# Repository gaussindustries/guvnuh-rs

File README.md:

# Guv'nuh — Micro-Grid Governor Control Platform

A Rust, bare-metal-to-browser control system for a laboratory micro-grid generator set. A hard-real-time STM32H753 governs the machine; an ESP32 bridges it to a Dioxus server and a desktop operator console. Built as the engineering centerpiece for [Gauss Industries](https://gaussindustri.es).

---

## What it does

Guv'nuh closes the loop on a self-excited induction generator (SEIG) driven by a variable-speed prime mover: it holds speed and frequency against changing electrical load, sheds load safely on fault, and streams a full electrical picture — per-phase voltage and current, real power, power factor, DC-bus state — to an operator in real time.

The architecture follows one principle: **the STM32 runs the machine; everything else observes and commands.** Safety-critical decisions (overspeed, load rejection, over-voltage/current) are computed and acted on locally, on-device, with no dependence on the network being up. The ESP32 relays; the server stores; the terminal analyzes. Comms can drop without the machine ever losing control.

---

## System architecture

```
  ┌─────────────┐   UART/COBS    ┌──────────┐    TCP/COBS    ┌──────────────┐   HTTP    ┌───────────────┐
  │  STM32H753  │◄──────────────►│  ESP32   │◄──────────────►│ Dioxus Server│◄─────────►│ Desktop Term. │
  │  (RTIC 2)   │  telemetry ▲   │ (Embassy)│  telemetry ▲   │   + SurrealDB│           │  (Dioxus)     │
  │  the machine│  commands  ▼   │  bridge  │  commands  ▼   │   store/API  │           │  operator UI  │
  └─────────────┘                └──────────┘                └──────────────┘           └───────────────┘
        │
        ├─ dual ADS131M04 (3-phase V/I + DC bus) — coherent sampling
        ├─ TIM1 PWM → prime-mover drive
        ├─ TIM2 QEI → speed encoder
        └─ ordered load bank (2-step resistive, series-ground)
```

**One wire format, end to end.** Every hop serializes the same `shared` crate types with `postcard` + COBS framing — no translation layers, no schema drift between tiers (the whole set rebuilds together when the wire types change).

---

## The STM32H753 firmware — the real-time core

Written against **RTIC 2**, priority-scheduled so the machine stays in tolerance regardless of what else is happening:

| Priority | Task | Rate | Job |
|---|---|---|---|
| 3 | ADC DRDY ISR | ~4 kSPS | Read both ADCs coherently, accumulate sum-of-squares |
| 3 | UART4 RX ISR | event | Drain FIFO, COBS-decode commands into a queue |
| 2 | Safety supervisor | 500 Hz | Overspeed trip + fast electrical protection + load-rejection detection |
| 1 | Control loop | 100 Hz | Governing, full ADC finalize, telemetry assembly |

**Three-phase electrical measurement.** Two ADS131M04 24-bit delta-sigma ADCs share one SPI bus with tied SYNC lines, so all eight channels sample the *same instant* — essential for real-power math (V×I per phase must be coherent). The STM32 computes only the control-critical scalars locally (RMS V/I, real power, PF, frequency, DC bus); harmonics and deep analysis are left to the terminal. Sample rate is a single tunable constant, sized against measured worst-case execution time.

**Load rejection — the fast local path.** A sudden real-power drop means the generator has been unloaded and will overspeed (the defining hazard for a turbine prime mover). The 500 Hz supervisor watches total real power and reacts in-loop — shedding load and faulting — with no network round-trip. This is why the electrical measurements live on the STM32 and not just in telemetry.

**Ordered load bank.** A two-step resistive bank whose second stage draws its ground return *through* the first, so the switching order is a hard electrical constraint. The firmware models this as a state machine that makes an invalid state unrepresentable: it refuses to engage step 2 without step 1, sheds gracefully (2 then 1) under normal operation, and sheds immediately (open 1, dropping both) on E-stop or fault.

---

## The ESP32 bridge

An **Embassy** async firmware that does one job well: shuttle framed bytes between the STM32's UART and a TCP socket to the server, intercepting the link-layer handshake locally so a reboot on either side re-syncs without disturbing the machine. Deliberately dumb — it holds no control logic, matching the "STM32 runs the machine" principle.

---

## Server & operator console

**Dioxus fullstack server** (axum + SurrealDB): ingests telemetry over TCP, stores trials, and exposes a hardware-control API. Telemetry x-axes are derived from a **server-side frame index**, not the device clock — eliminating boot-offset artifacts by construction.

**Desktop operator terminal** (Dioxus): live governing controls (manual / open-loop / closed-loop / scripted profiles), real-time charts (RPM, three-phase voltage and current on shared axes, power and phase-alignment error), a load-bank panel that mirrors the firmware's ordered state machine in the UI, and a trials browser that replays any recorded run with every electrical channel toggleable.

**Scripted profiles** let an operator define an RPM trajectory with load steps scheduled at specific breakpoints — "at t=5s apply half load, at t=10s go full, at t=15s shed" — executed on-device with the ordered switching still enforced.

---

## Tech stack

- **Firmware:** Rust, `no_std`, RTIC 2 (STM32H753), Embassy (ESP32)
- **Wire format:** `postcard` + COBS over UART and TCP; shared type crate
- **Server:** Rust, Dioxus fullstack, axum, SurrealDB (raw HTTP transport)
- **Terminal:** Rust, Dioxus desktop
- **Sensing:** dual TI ADS131M04, external 8.192 MHz coherent clock
- **Networking:** WireGuard-gated admin plane, nginx reverse proxy

---

## Status

Operational: full command + telemetry pipeline live across all four tiers; load bank commanding end-to-end with ordered-switching and E-stop shedding verified in hardware; governing loop running closed on the bench. Three-phase ADC front-end is wired into the firmware (flag-gated) and pending analog front-end bring-up.

**Roadmap:** phase-lock to a grid reference (the alignment view is built and waiting), EtherCAT fieldbus, a SIL-2 certification path, and a micro steam turbine prime mover.

---

## License

© Gauss Industries. All rights reserved.

*Integrity · Innovation · Invention*

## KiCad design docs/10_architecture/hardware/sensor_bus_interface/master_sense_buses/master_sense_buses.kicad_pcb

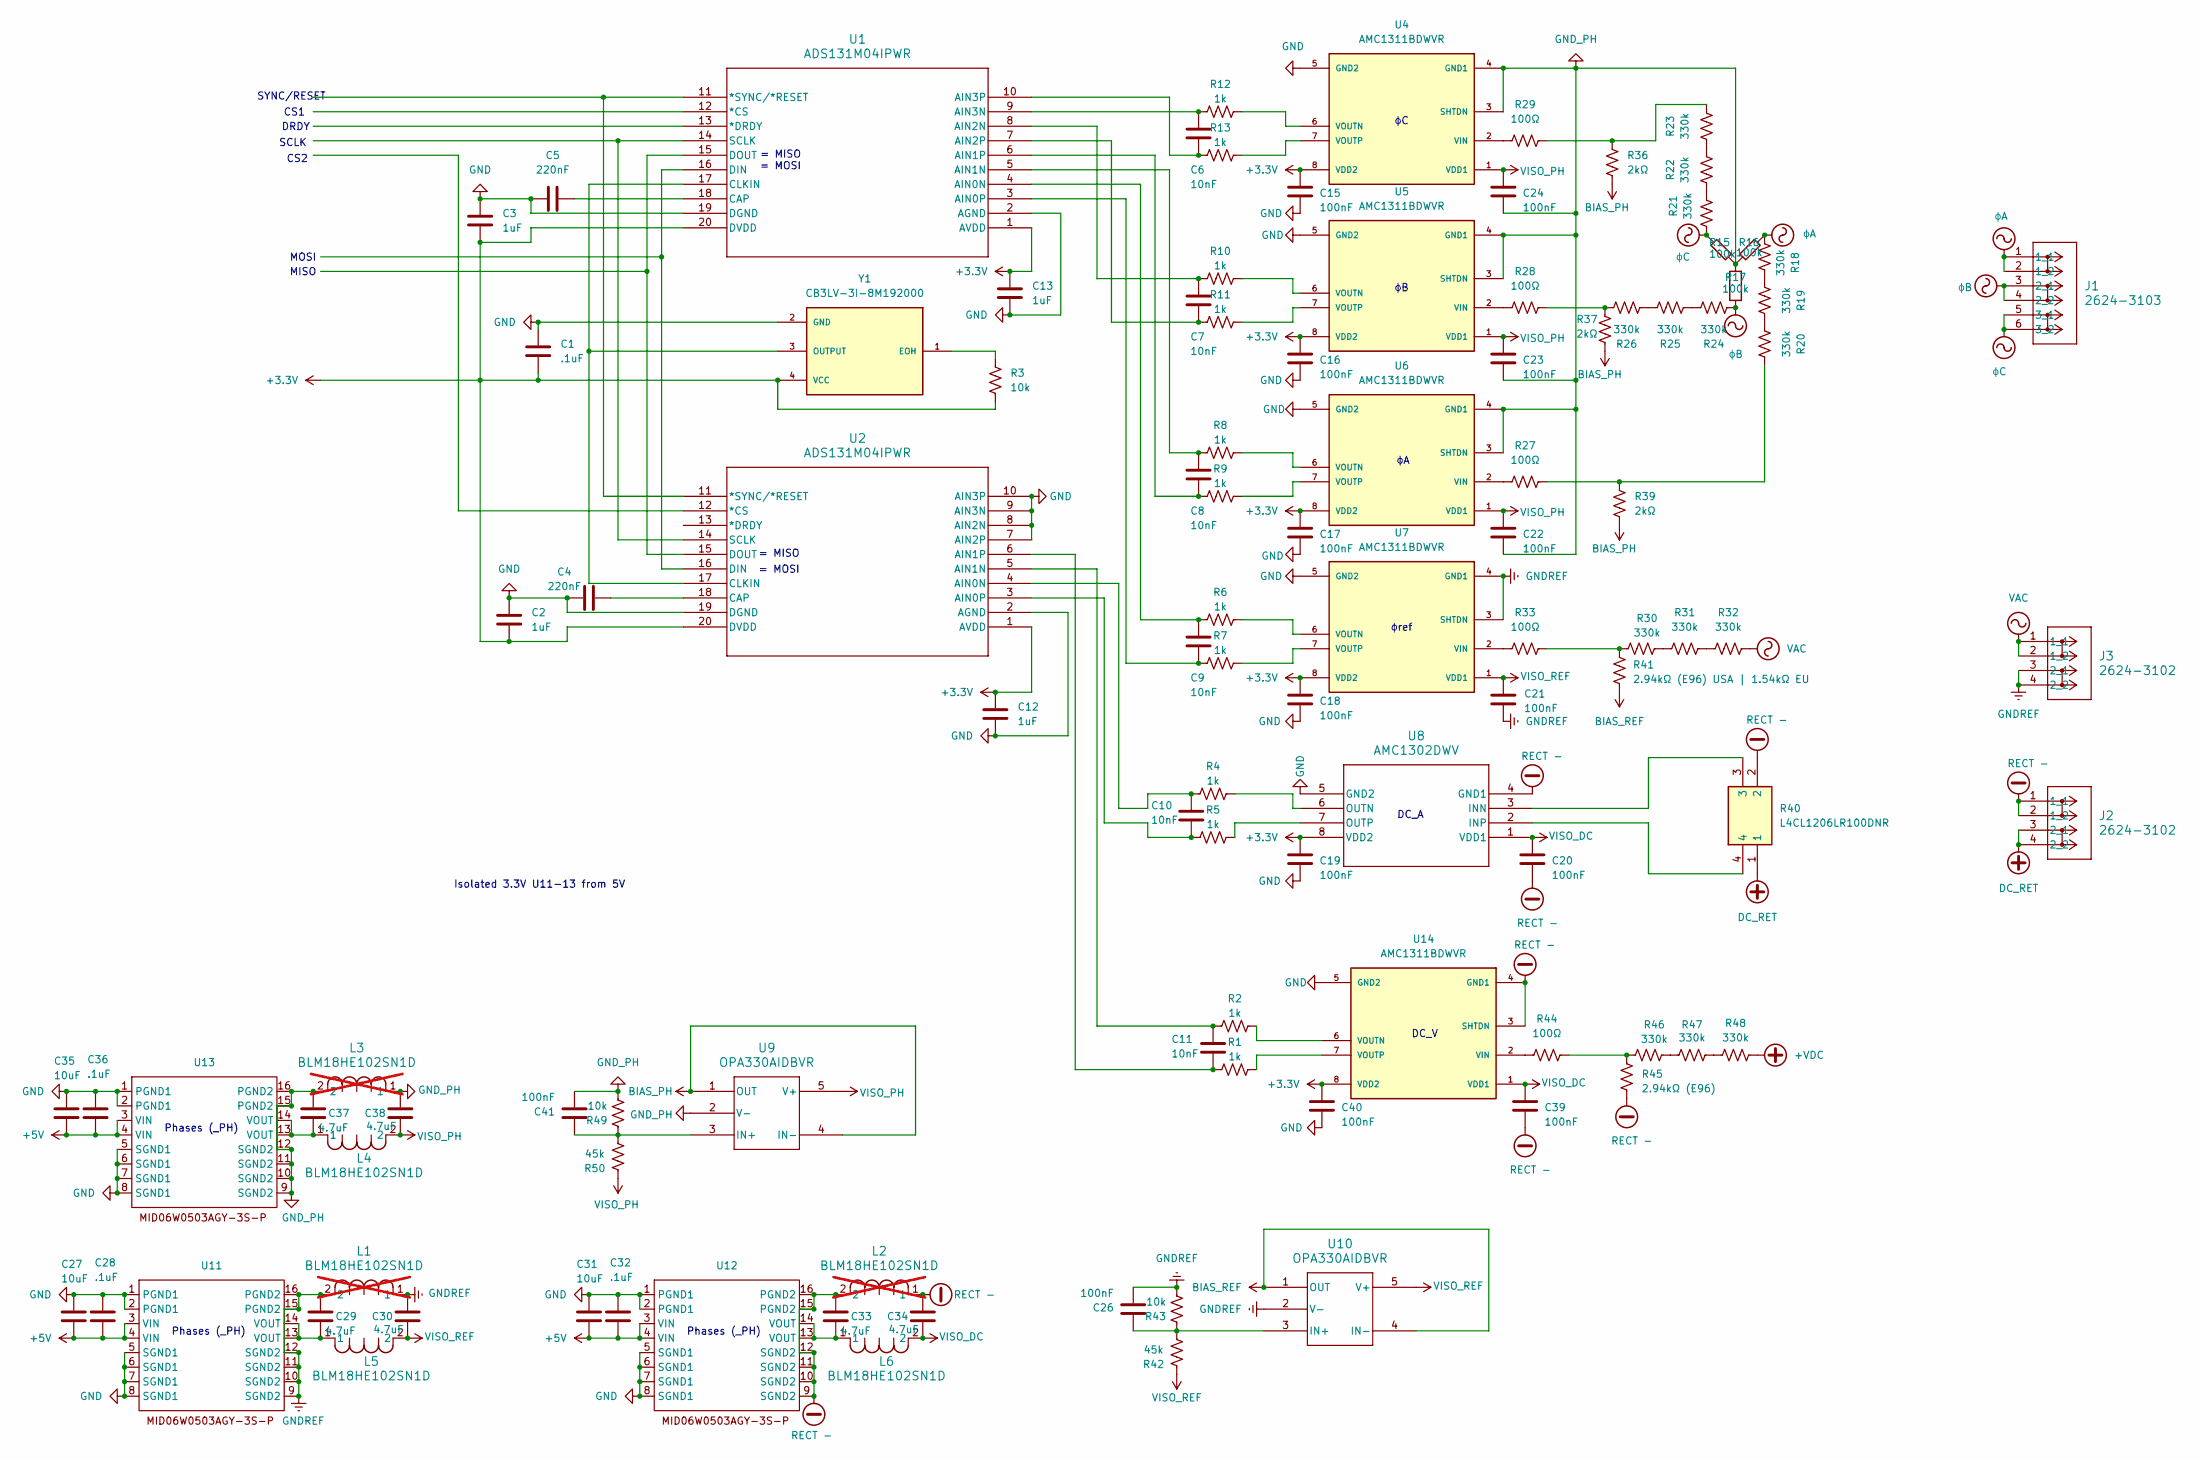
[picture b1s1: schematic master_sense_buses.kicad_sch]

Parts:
C1, C28, C32, C36: .1uF; C_0402_1005Metric
C2, C3, C12, C13: 1uF; C_0603_1608Metric
C4, C5: 220nF; C_0201_0603Metric
C6, C7, C8, C9, C10, C11: 10nF; C_0603_1608Metric
C15, C16, C17, C18, C19, C20, C21, C22, C23, C24, C39, C40: 100nF; C_0402_1005Metric
C26, C41: 100nF; C_0201_0603Metric
C27, C31, C35: 10uF; C_0805_2012Metric
C29, C30, C33, C34, C37, C38: 4.7uF; C_0603_1608Metric
J1: 2624-3103; CONN3_2624-3103_WAG
J2, J3: 2624-3102; CONN2_2624-3102_WAG
L1, L2, L3: BLM18HE102SN1D; IND_BLM18_0603_MUR-L; not fitted
L4, L5, L6: BLM18HE102SN1D; IND_BLM18_0603_MUR-L
R1, R2, R4, R5, R6, R7, R8, R9, R10, R11, R12, R13: 1k; R_0603_1608Metric
R3, R43, R49: 10k; R_0201_0603Metric
R15, R16, R17: 100k; R_Axial_DIN0414_L11.9mm_D4.5mm_P15.24mm_Horizontal
R18, R19, R20, R21, R22, R23, R24, R25, R26, R30, R31, R32, R46, R47, R48: 330k; R_1206_3216Metric
R27, R28, R29, R33, R44: 100Ω; R_0805_2012Metric
R36, R37, R39: 2kΩ; R_1206_3216Metric
R40: L4CL1206LR100DNR; Mouser Part Number 576-L4CL1206LR100DNR
R41: 2.94kΩ (E96) USA | 1.54kΩ EU; R_0402_1005Metric
R42, R50: 45k; R_0603_1608Metric
R45: 2.94kΩ (E96); R_0402_1005Metric
U1, U2: ADS131M04IPWR; PW20_TEX-L
U4, U5, U6, U7, U14: AMC1311BDWVR; SOIC127P1150X280-8N; PARTREV A
U8: AMC1302DWV; SOIC8_DMV_TEX-L
U9, U10: OPA330AIDBVR; DBV5
U11, U12, U13: SOIC-16W_7.5x10.3mm_P1.27mm_MPS_SOICW-16
Y1: CB3LV-3I-8M192000; OSC_CB3LV-3I-8M192000; PARTREV NA

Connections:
+3.3V: C1.2, C2.2, C3.2, C12.1, C13.1, C15.1, C16.1, C17.1, C18.1, C19.1, C40.1, R3.2, U1.1 (AVDD), U1.20 (DVDD), U2.1 (AVDD), U2.20 (DVDD), U4.8 (VDD2), U5.8 (VDD2), U6.8 (VDD2), U7.8 (VDD2), U8.8 (VDD2), U14.8 (VDD2), Y1.4 (VCC)
+5V: C27.2, C28.2, C31.2, C32.2, C35.2, C36.2, U11.3 (VIN), U11.4 (VIN), U12.3 (VIN), U12.4 (VIN), U13.3 (VIN), U13.4 (VIN)
+VDC: R48.1; also elsewhere on the board
BIAS_PH: R36.2, R37.2, R39.2, U9.1 (OUT), U9.4 (IN-)
BIAS_REF: R41.2, U10.1 (OUT), U10.4 (IN-)
DC_RET: J2.3 (2_1), J2.4 (2_2), R40.1
GND: C1.1, C2.1, C3.1, C4.2, C5.1, C12.2, C13.2, C15.2, C16.2, C17.2, C18.2, C19.2, C27.1, C28.1, C31.1, C32.1, C35.1, C36.1, C40.2, U1.2 (AGND), U1.19 (DGND), U2.2 (AGND), U2.7 (AIN2P), U2.8 (AIN2N), U2.9 (AIN3N), U2.10 (AIN3P), U2.19 (DGND), U4.5 (GND2), U5.5 (GND2), U6.5 (GND2), U7.5 (GND2), U8.5 (GND2), U11.1 (PGND1), U11.2 (PGND1), U11.5 (SGND1), U11.6 (SGND1), U11.7 (SGND1), U11.8 (SGND1), U12.1 (PGND1), U12.2 (PGND1), U12.5 (SGND1), U12.6 (SGND1), U12.7 (SGND1), U12.8 (SGND1), U13.1 (PGND1), U13.2 (PGND1), U13.5 (SGND1), U13.6 (SGND1), U13.7 (SGND1), U13.8 (SGND1), U14.5 (GND2), Y1.2 (GND)
GNDREF: C21.2, C26.2, C29.1, C30.1, J3.3 (2_1), J3.4 (2_2), L1.1, L1.2, R43.2, U7.3 (SHTDN), U7.4 (GND1), U10.2 (V-), U11.9 (SGND2), U11.10 (SGND2), U11.11 (SGND2), U11.12 (SGND2), U11.15 (PGND2), U11.16 (PGND2)
GND_PH: C22.2, C23.2, C24.2, C37.1, C38.1, C41.2, L3.1, L3.2, R15.1, R16.2, R17.2, R49.2, U4.3 (SHTDN), U4.4 (GND1), U5.3 (SHTDN), U5.4 (GND1), U6.3 (SHTDN), U6.4 (GND1), U9.2 (V-), U13.9 (SGND2), U13.10 (SGND2), U13.11 (SGND2), U13.12 (SGND2), U13.15 (PGND2), U13.16 (PGND2)
unnamed: C29.2, L5.1, U11.13 (VOUT), U11.14 (VOUT)
unnamed: C33.2, L6.1, U12.13 (VOUT), U12.14 (VOUT)
unnamed: C37.2, L4.1, U13.13 (VOUT), U13.14 (VOUT)
unnamed: R18.1, R19.2
unnamed: R19.1, R20.2
unnamed: R20.1, R27.1, R39.1
unnamed: R21.1, R22.2
unnamed: R22.1, R23.2
unnamed: R23.1, R29.1, R36.1
unnamed: R24.1, R25.2
unnamed: R25.1, R26.2
unnamed: R26.1, R28.1, R37.1
unnamed: R30.1, R31.2
unnamed: R30.2, R33.1, R41.1
unnamed: R31.1, R32.2
unnamed: R44.1, R45.1, R46.2
unnamed: R46.1, R47.2
unnamed: R47.1, R48.2
unnamed: U1.11 (*SYNC/*RESET), U2.11 (*SYNC/*RESET)
unnamed: C9.1, R6.2, U1.4 (AIN0N)
unnamed: C9.2, R7.2, U1.3 (AIN0P)
unnamed: C8.1, R8.2, U1.5 (AIN1N)
unnamed: C8.2, R9.2, U1.6 (AIN1P)
unnamed: C7.1, R10.2, U1.8 (AIN2N)
unnamed: C7.2, R11.2, U1.7 (AIN2P)
unnamed: C6.1, R12.2, U1.9 (AIN3N)
unnamed: C6.2, R13.2, U1.10 (AIN3P)
unnamed: C5.2, U1.18 (CAP)
unnamed: U1.17 (CLKIN), U2.17 (CLKIN), Y1.3 (OUTPUT)
unnamed: U1.16 (DIN), U2.16 (DIN)
unnamed: U1.15 (DOUT), U2.15 (DOUT)
unnamed: U1.14 (SCLK), U2.14 (SCLK)
unnamed: C10.1, R4.2, U2.4 (AIN0N)
unnamed: C10.2, R5.2, U2.3 (AIN0P)
unnamed: C11.1, R2.2, U2.5 (AIN1N)
unnamed: C11.2, R1.2, U2.6 (AIN1P)
unnamed: C4.1, U2.18 (CAP)
unnamed: R29.2, U4.2 (VIN)
unnamed: R12.1, U4.6 (VOUTN)
unnamed: R13.1, U4.7 (VOUTP)
unnamed: R28.2, U5.2 (VIN)
unnamed: R10.1, U5.6 (VOUTN)
unnamed: R11.1, U5.7 (VOUTP)
unnamed: R27.2, U6.2 (VIN)
unnamed: R8.1, U6.6 (VOUTN)
unnamed: R9.1, U6.7 (VOUTP)
unnamed: R33.2, U7.2 (VIN)
unnamed: R6.1, U7.6 (VOUTN)
unnamed: R7.1, U7.7 (VOUTP)
unnamed: R40.3, U8.3 (INN)
unnamed: R40.4, U8.2 (INP)
unnamed: R4.1, U8.6 (OUTN)
unnamed: R5.1, U8.7 (OUTP)
unnamed: C41.1, R49.1, R50.1, U9.3 (IN+)
unnamed: C26.1, R42.1, R43.1, U10.3 (IN+)
unnamed: R44.2, U14.2 (VIN)
unnamed: R2.1, U14.6 (VOUTN)
unnamed: R1.1, U14.7 (VOUTP)
unnamed: R3.1, Y1.1 (EOH)
RECT -: C20.2, C33.1, C34.1, C39.2, J2.1 (1_1), J2.2 (1_2), L2.1, L2.2, R40.2, R45.2, U8.4 (GND1), U12.9 (SGND2), U12.10 (SGND2), U12.11 (SGND2), U12.12 (SGND2), U12.15 (PGND2), U12.16 (PGND2), U14.3 (SHTDN), U14.4 (GND1)
VAC: J3.1 (1_1), J3.2 (1_2), R32.1
VISO_DC: C20.1, C34.2, C39.1, L6.2, U8.1 (VDD1), U14.1 (VDD1)
VISO_PH: C22.1, C23.1, C24.1, C38.2, L4.2, R50.2, U4.1 (VDD1), U5.1 (VDD1), U6.1 (VDD1), U9.5 (V+)
VISO_REF: C21.1, C30.2, L5.2, R42.2, U7.1 (VDD1), U10.5 (V+)
ϕA: J1.1 (1_1), J1.2 (1_2), R16.1, R18.2
ϕB: J1.3 (2_1), J1.4 (2_2), R17.1, R24.2
ϕC: J1.5 (3_1), J1.6 (3_2), R15.2, R21.2

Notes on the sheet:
Phases (_PH)
= MISO
= MOSI
DC_V
SCLK
MOSI
DC_A
DRDY
Isolated 3.3V U11-13 from 5V
CS2
ϕref
MISO
CS1
SYNC/RESET

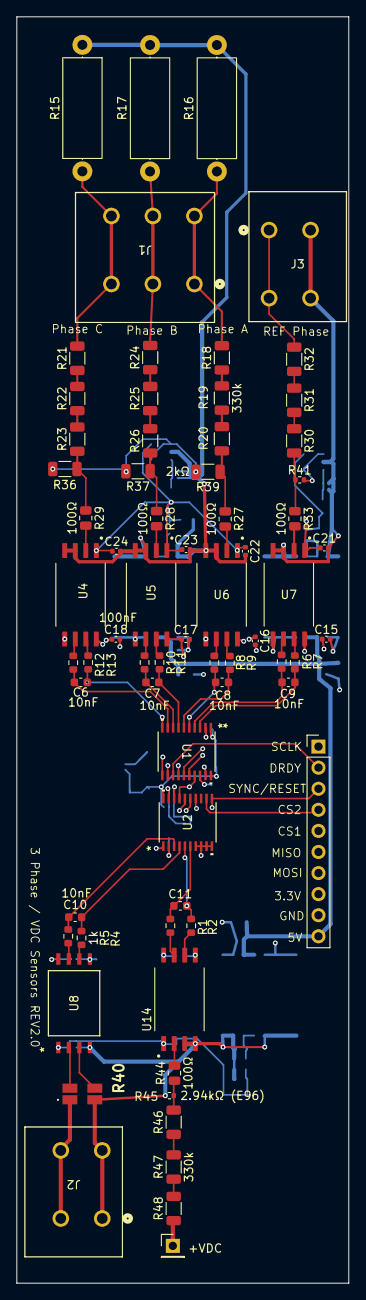
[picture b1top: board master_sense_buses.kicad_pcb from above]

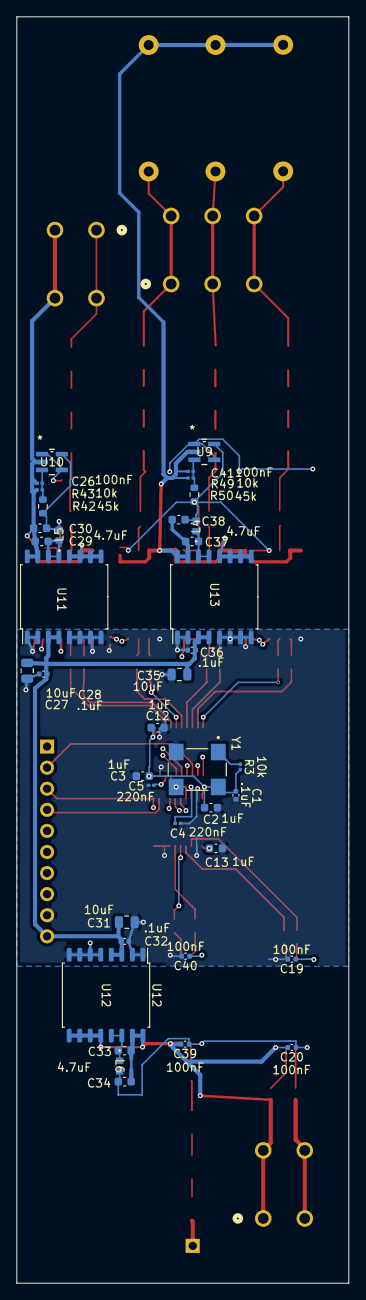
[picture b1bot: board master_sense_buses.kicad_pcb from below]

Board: 4 copper layers, 40.0 x 152.6 mm, 106 parts (39 on the bottom side), 76 nets.

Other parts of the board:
+VDC: PinHeader_1x01_P2.54mm_Vertical

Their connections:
+VDC: +VDC.1; also elsewhere on the board

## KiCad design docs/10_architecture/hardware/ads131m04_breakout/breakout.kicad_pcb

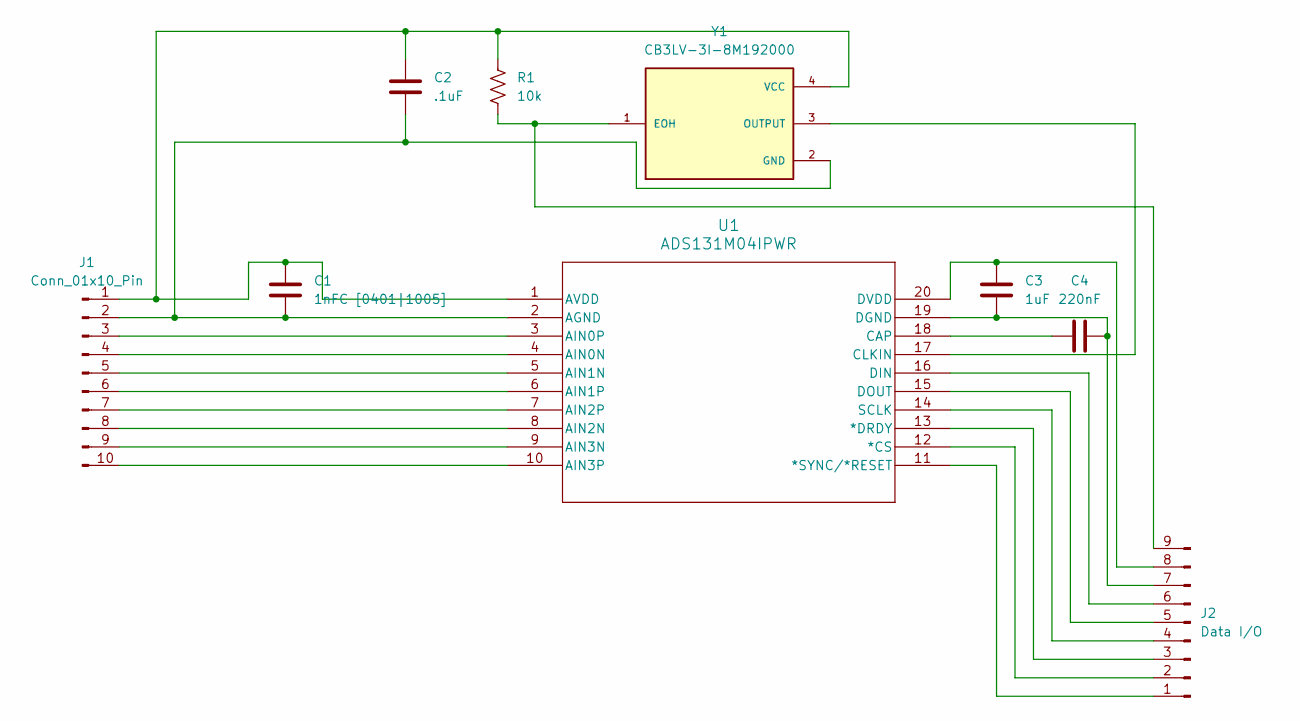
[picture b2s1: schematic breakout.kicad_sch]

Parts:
C1: 1nFC [0401|1005]; C_0402_1005Metric
C2: .1uF; C_0201_0603Metric
C3: 1uF; C_0201_0603Metric
C4: 220nF; C_0402_1005Metric
J1: Conn_01x10_Pin; PinHeader_1x10_P2.54mm_Vertical
J2: Data I/O; PinHeader_1x09_P2.54mm_Vertical
R1: 10k; R_0201_0603Metric
U1: ADS131M04IPWR; PW20_TEX-L
Y1: CB3LV-3I-8M192000; OSC_CB3LV-3I-8M192000; PARTREV NA

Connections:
unnamed: C1.1, C2.1, J1.1, R1.1, U1.1 (AVDD), Y1.4 (VCC)
unnamed: C1.2, C2.2, J1.2, U1.2 (AGND), Y1.2 (GND)
unnamed: J1.3, U1.3 (AIN0P)
unnamed: J1.4, U1.4 (AIN0N)
unnamed: J1.5, U1.5 (AIN1N)
unnamed: J1.6, U1.6 (AIN1P)
unnamed: J1.7, U1.7 (AIN2P)
unnamed: J1.8, U1.8 (AIN2N)
unnamed: J1.9, U1.9 (AIN3N)
unnamed: J1.10, U1.10 (AIN3P)
unnamed: J2.1, U1.11 (*SYNC/*RESET)
unnamed: J2.2, U1.12 (*CS)
unnamed: J2.3, U1.13 (*DRDY)
unnamed: J2.4, U1.14 (SCLK)
unnamed: J2.5, U1.15 (DOUT)
unnamed: J2.6, U1.16 (DIN)
unnamed: C3.2, C4.2, J2.7, U1.19 (DGND)
unnamed: C3.1, J2.8, U1.20 (DVDD)
unnamed: J2.9, R1.2, Y1.1 (EOH)
unnamed: C4.1, U1.18 (CAP)
unnamed: U1.17 (CLKIN), Y1.3 (OUTPUT)

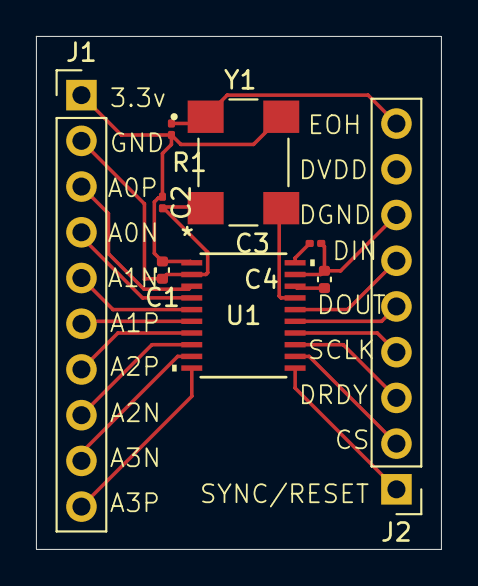
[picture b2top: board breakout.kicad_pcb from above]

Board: 2 copper layers, 22.5 x 28.5 mm, 9 parts (0 on the bottom side), 21 nets.

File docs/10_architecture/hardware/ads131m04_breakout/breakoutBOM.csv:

Reference,Qty,Value,DNP,Exclude from BOM,Exclude from Board,Exclude from Simulation,Exclude from Position Files,Footprint,Datasheet
C1,1,1nFC [0401|1005],0.01294,,,,${EXCLUDE_FROM_POS_FILES},Capacitor_SMD:C_0402_1005Metric,
C2,1,.1uF,0.00622,,,,${EXCLUDE_FROM_POS_FILES},Capacitor_SMD:C_0201_0603Metric,
C3,1,1uF,0.11860,,,,${EXCLUDE_FROM_POS_FILES},Capacitor_SMD:C_0201_0603Metric,
C4,1,220nF,0.00874,,,,${EXCLUDE_FROM_POS_FILES},Capacitor_SMD:C_0402_1005Metric,
J1,1,Conn_01x19_Pin,11.4,,,,${EXCLUDE_FROM_POS_FILES},Connector_PinHeader_2.54mm:PinHeader_1x10_P2.54mm_Vertical,
R1,1,10k,0.01305,,,,${EXCLUDE_FROM_POS_FILES},Resistor_SMD:R_0201_0603Metric,https://www.vishay.com/docs/20035/dcrcwe3.pdf
U1,1,ADS131M04IPWR,5.29,,,,${EXCLUDE_FROM_POS_FILES},Analog_DAC:PW20_TEX-L,https://www.ti.com/lit/gpn/ads131m04
Y1,1,CB3LV-3I-8M192000,1.38,,9.292 each board,,${EXCLUDE_FROM_POS_FILES},Oscillator:OSC_CB3LV-3I-8M192000,
,,,6.82081,with pins = 18.22081,w board wo pins = 16.11281,board w pins = 27.51281,,,

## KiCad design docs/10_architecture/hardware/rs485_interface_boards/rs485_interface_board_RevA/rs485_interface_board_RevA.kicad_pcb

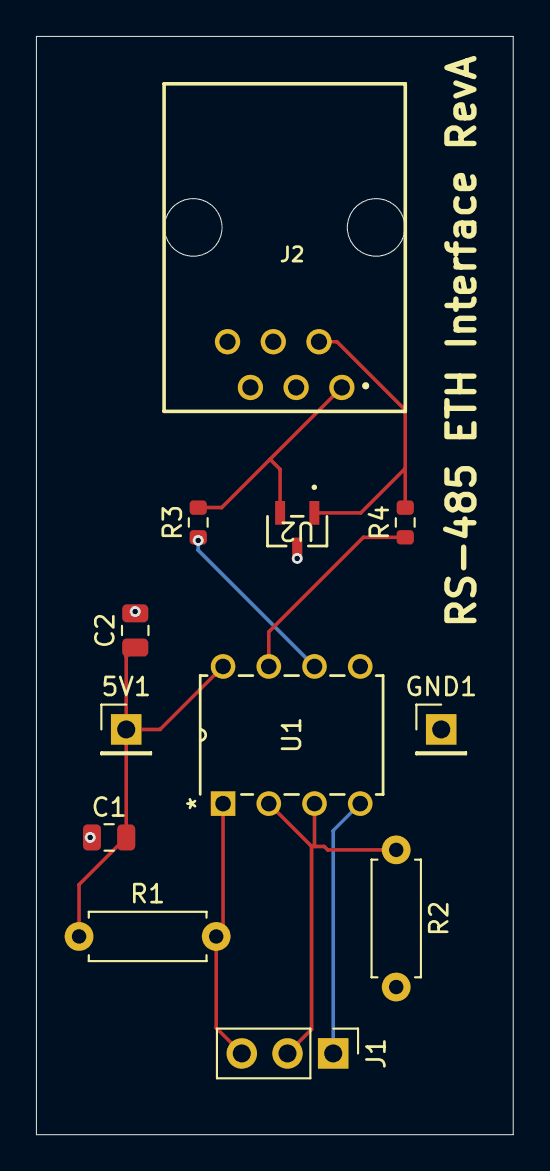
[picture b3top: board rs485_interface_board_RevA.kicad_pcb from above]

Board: 2 copper layers, 26.5 x 61.0 mm, 12 parts (0 on the bottom side), 9 nets.

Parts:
5V1: Conn_01x01; PinHeader_1x01_P2.54mm_Vertical
C1, C2: 100 nf; C_0805_2012Metric
GND1: Conn_01x01; PinHeader_1x01_P2.54mm_Vertical
J1: Conn_01x03; PinHeader_1x03_P2.54mm_Vertical
J2: 615006141121
R1, R2: 10k; R_Axial_DIN0207_L6.3mm_D2.5mm_P7.62mm_Horizontal
R3, R4: 10 Ohm; R_0603_1608Metric
U1: SN65HVD3082EP; sn65hvd3082
U2: SM712.TCT; SOT23_SEM

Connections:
+5V: 5V1.1, C1.2, C2.1, R1.1, U1.8 (VCC)
GND: C1.1, C2.2, GND1.1, J2.3, R2.2, U1.5 (GND), U2.3
unnamed: J1.1, U1.4 (D)
unnamed: J1.2, R2.1, U1.2 (*RE), U1.3 (DE)
unnamed: J1.3, R1.2, U1.1 (R)
unnamed: J2.1, R3.2, U2.2
unnamed: J2.2, R4.2, U2.1
unnamed: R3.1, U1.6 (A)
unnamed: R4.1, U1.7 (B)

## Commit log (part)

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2025-07-07 Init commit – charter, diagrams, CI, docs
2025-07-09 updated master sketch, organized, min vibration
2025-07-09 Added ESP32 Reference Material
2025-07-09 Paved roads to success
2025-10-26 configured linker scripts, simple led blink test
2025-10-26 updated build, prog, & debug commands
2025-10-26 fixed ld2 not blinking
2025-12-11 updated from c/cpp branch
2026-01-15 updated state mod.rs, embedded boot sequence in it's respective file, refined main.rs
2026-01-20 implemented basic logic for pwm for motor spin
2026-02-24 added relay pin & basic safety functionality
2026-03-03 implemented RPM monitor & amt102-v inputs via QEI
2026-03-11 switched to probe-rs for flash/defmt, fixed u64 mismatch in mono timing, fixed negative rpm
2026-03-11 improved rpm calculation
2026-03-11 initialized esp32 logic & build, cleaned config for stm32
2026-03-12 added LED indication for rx (esp32)
2026-03-12 implemented basic UART handshake to ensure stm32 will wait for esp32, or vise versa
2026-03-12 implemented STM32 → UART → ESP32 → WiFi → TCP datapipline
2026-03-17 updated to use data pipeline: STM32 → UART → ESP32 → TCP → Server → SurrealDB
2026-03-21 refined logic to recieve Start command via desktop terminal
2026-03-22 updated readme to reflect current system
2026-05-28 added motor generics, prelude for granular control of trials/running state, live control, updated models to reflect changes
